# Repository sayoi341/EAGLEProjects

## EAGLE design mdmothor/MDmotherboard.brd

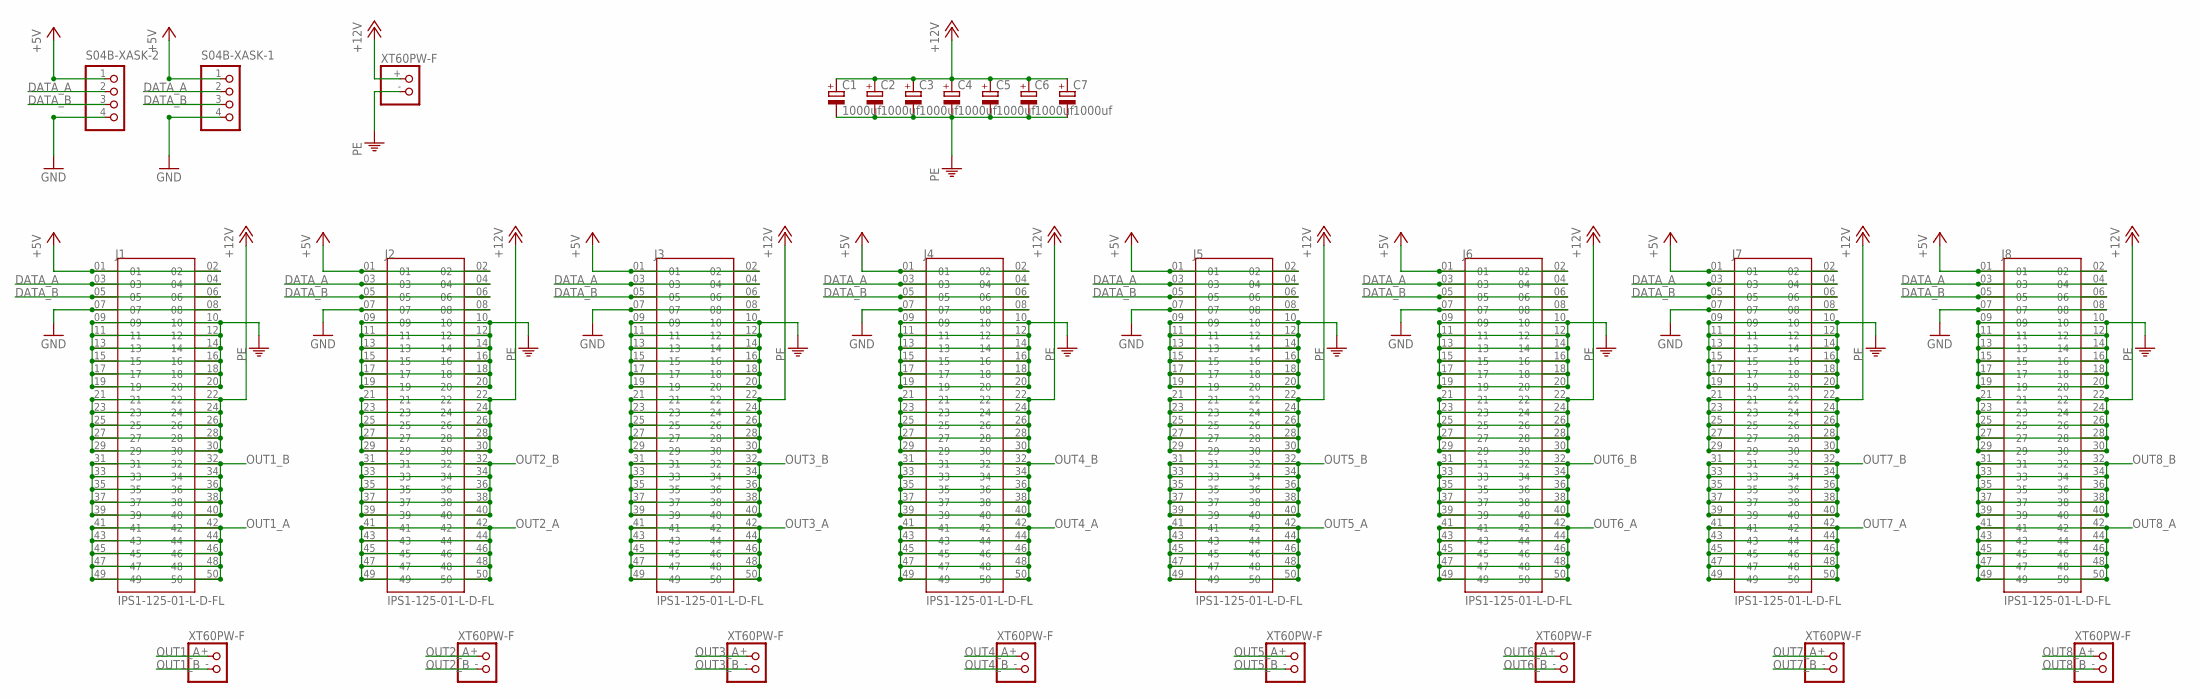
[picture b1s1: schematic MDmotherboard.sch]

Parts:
C1, C2, C3, C4, C5, C6, C7: 1000uf; E3,5-10
J1, J2, J3, J4, J5, J6, J7, J8: IPS1-125-01-L-D-FL; SAMTEC_IPS1-125-01-L-D-FL
S04B-XASK-1, S04B-XASK-2: S4B-XASK-1
U$1, U$2, U$3, U$4, U$5, U$6, U$7, U$8, U$9: XT60PW-F

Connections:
+5V: J1.01, J1.02, J2.01, J2.02, J3.01, J3.02, J4.01, J4.02, J5.01, J5.02, J6.01, J6.02, J7.01, J7.02, J8.01, J8.02, S04B-XASK-1.1, S04B-XASK-2.1
+12V: C1.+, C2.+, C3.+, C4.+, C5.+, C6.+, C7.+, J1.21, J1.22, J1.23, J1.24, J1.25, J1.26, J1.27, J1.28, J1.29, J1.30, J2.21, J2.22, J2.23, J2.24, J2.25, J2.26, J2.27, J2.28, J2.29, J2.30, J3.21, J3.22, J3.23, J3.24, J3.25, J3.26, J3.27, J3.28, J3.29, J3.30, J4.21, J4.22, J4.23, J4.24, J4.25, J4.26, J4.27, J4.28, J4.29, J4.30, J5.21, J5.22, J5.23, J5.24, J5.25, J5.26, J5.27, J5.28, J5.29, J5.30, J6.21, J6.22, J6.23, J6.24, J6.25, J6.26, J6.27, J6.28, J6.29, J6.30, J7.21, J7.22, J7.23, J7.24, J7.25, J7.26, J7.27, J7.28, J7.29, J7.30, J8.21, J8.22, J8.23, J8.24, J8.25, J8.26, J8.27, J8.28, J8.29, J8.30, U$1.+
DATA_A: J1.03, J1.04, J2.03, J2.04, J3.03, J3.04, J4.03, J4.04, J5.03, J5.04, J6.03, J6.04, J7.03, J7.04, J8.03, J8.04, S04B-XASK-1.2, S04B-XASK-2.2
DATA_B: J1.05, J1.06, J2.05, J2.06, J3.05, J3.06, J4.05, J4.06, J5.05, J5.06, J6.05, J6.06, J7.05, J7.06, J8.05, J8.06, S04B-XASK-1.3, S04B-XASK-2.3
GND: J1.07, J1.08, J2.07, J2.08, J3.07, J3.08, J4.07, J4.08, J5.07, J5.08, J6.07, J6.08, J7.07, J7.08, J8.07, J8.08, S04B-XASK-1.4, S04B-XASK-2.4
OUT1_A: J1.41, J1.42, J1.43, J1.44, J1.45, J1.46, J1.47, J1.48, J1.49, J1.50, U$2.+
OUT1_B: J1.31, J1.32, J1.33, J1.34, J1.35, J1.36, J1.37, J1.38, J1.39, J1.40, U$2.-
OUT2_A: J2.41, J2.42, J2.43, J2.44, J2.45, J2.46, J2.47, J2.48, J2.49, J2.50, U$3.+
OUT2_B: J2.31, J2.32, J2.33, J2.34, J2.35, J2.36, J2.37, J2.38, J2.39, J2.40, U$3.-
OUT3_A: J3.41, J3.42, J3.43, J3.44, J3.45, J3.46, J3.47, J3.48, J3.49, J3.50, U$4.+
OUT3_B: J3.31, J3.32, J3.33, J3.34, J3.35, J3.36, J3.37, J3.38, J3.39, J3.40, U$4.-
OUT4_A: J4.41, J4.42, J4.43, J4.44, J4.45, J4.46, J4.47, J4.48, J4.49, J4.50, U$5.+
OUT4_B: J4.31, J4.32, J4.33, J4.34, J4.35, J4.36, J4.37, J4.38, J4.39, J4.40, U$5.-
OUT5_A: J5.41, J5.42, J5.43, J5.44, J5.45, J5.46, J5.47, J5.48, J5.49, J5.50, U$6.+
OUT5_B: J5.31, J5.32, J5.33, J5.34, J5.35, J5.36, J5.37, J5.38, J5.39, J5.40, U$6.-
OUT6_A: J6.41, J6.42, J6.43, J6.44, J6.45, J6.46, J6.47, J6.48, J6.49, J6.50, U$7.+
OUT6_B: J6.31, J6.32, J6.33, J6.34, J6.35, J6.36, J6.37, J6.38, J6.39, J6.40, U$7.-
OUT7_A: J7.41, J7.42, J7.43, J7.44, J7.45, J7.46, J7.47, J7.48, J7.49, J7.50, U$8.+
OUT7_B: J7.31, J7.32, J7.33, J7.34, J7.35, J7.36, J7.37, J7.38, J7.39, J7.40, U$8.-
OUT8_A: J8.41, J8.42, J8.43, J8.44, J8.45, J8.46, J8.47, J8.48, J8.49, J8.50, U$9.+
OUT8_B: J8.31, J8.32, J8.33, J8.34, J8.35, J8.36, J8.37, J8.38, J8.39, J8.40, U$9.-
PE: C1.-, C2.-, C3.-, C4.-, C5.-, C6.-, C7.-, J1.09, J1.10, J1.11, J1.12, J1.13, J1.14, J1.15, J1.16, J1.17, J1.18, J1.19, J1.20, J2.09, J2.10, J2.11, J2.12, J2.13, J2.14, J2.15, J2.16, J2.17, J2.18, J2.19, J2.20, J3.09, J3.10, J3.11, J3.12, J3.13, J3.14, J3.15, J3.16, J3.17, J3.18, J3.19, J3.20, J4.09, J4.10, J4.11, J4.12, J4.13, J4.14, J4.15, J4.16, J4.17, J4.18, J4.19, J4.20, J5.09, J5.10, J5.11, J5.12, J5.13, J5.14, J5.15, J5.16, J5.17, J5.18, J5.19, J5.20, J6.09, J6.10, J6.11, J6.12, J6.13, J6.14, J6.15, J6.16, J6.17, J6.18, J6.19, J6.20, J7.09, J7.10, J7.11, J7.12, J7.13, J7.14, J7.15, J7.16, J7.17, J7.18, J7.19, J7.20, J8.09, J8.10, J8.11, J8.12, J8.13, J8.14, J8.15, J8.16, J8.17, J8.18, J8.19, J8.20, U$1.-

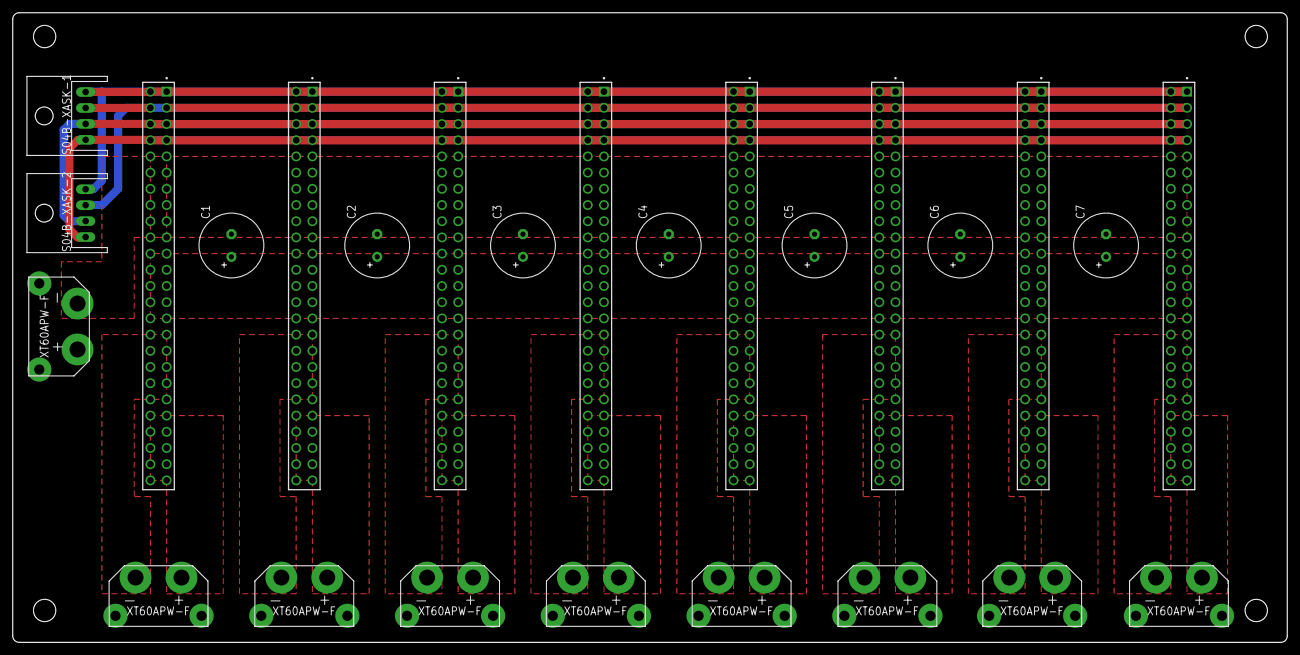
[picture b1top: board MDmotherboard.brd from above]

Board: 2 copper layers, 199.9 x 98.7 mm, 26 parts (0 on the bottom side), 22 nets.

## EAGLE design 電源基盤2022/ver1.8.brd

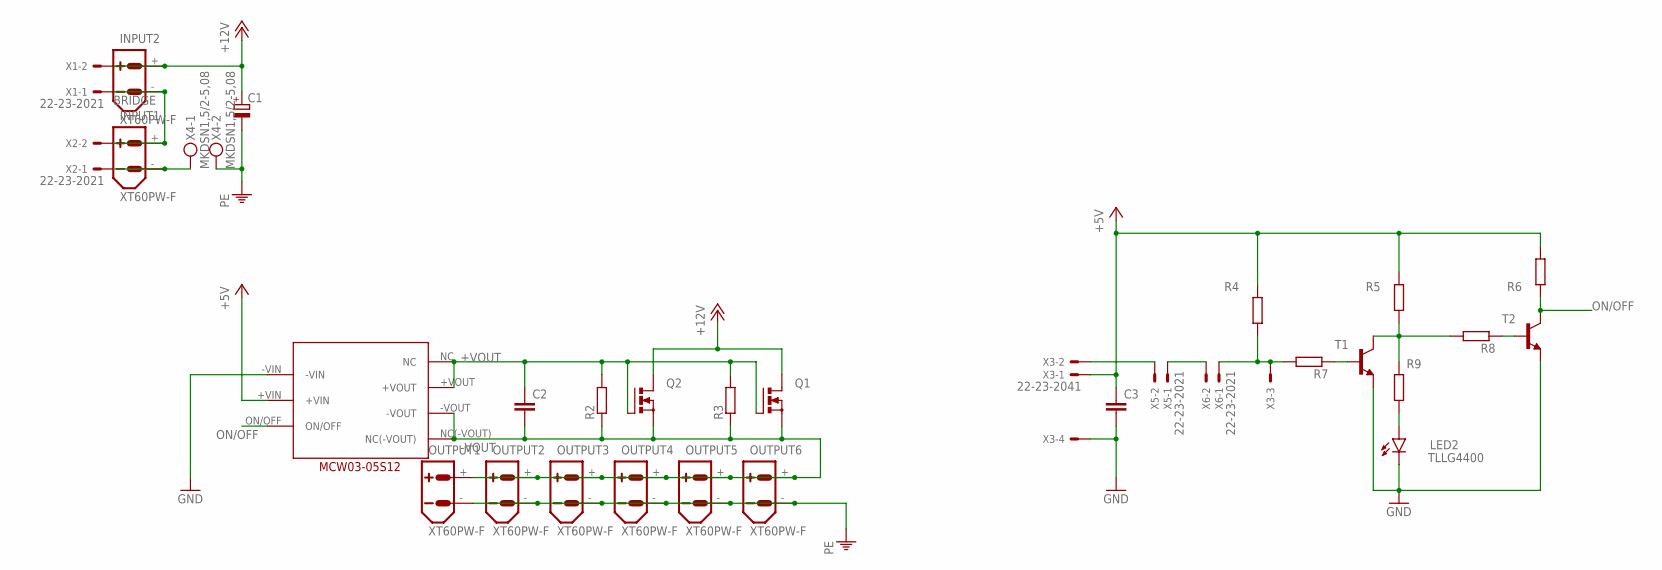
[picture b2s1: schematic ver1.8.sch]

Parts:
C1: CPOL-EUE3.5-10; E3,5-10
C2, C3: C-EU025-030X050; C025-030X050
INPUT1, INPUT2: XT60PW-F
LED2: TLLG4400; LED3MM
OUTPUT1, OUTPUT2, OUTPUT3, OUTPUT4, OUTPUT5, OUTPUT6: XT60PW-F
Q1, Q2: PMOSFET_NTO220BV; TO220BV
R2, R3, R4, R5, R6, R7, R8, R9: R-EU_0204/5; 0204/5
T1, T2: -NPN-TO92-ECB; TO92-ECB
U$3: MCW03-05S12
X1, X2, X5, X6: 22-23-2021
X3: 22-23-2041
X4: MKDSN1,5/2-5,08

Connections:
+5V: C3.1, R4.2, R5.2, R6.2, U$3.+VIN, X3.1
+12V: C1.+, INPUT2.+, Q1.D, Q2.D, X1.2
+VOUT: C2.1, Q1.G, Q2.G, R2.2, R3.2, U$3.+VOUT, U$3.NC
-VOUT: C2.2, OUTPUT1.+, OUTPUT2.+, OUTPUT3.+, OUTPUT4.+, OUTPUT5.+, OUTPUT6.+, Q1.S, Q2.S, R2.1, R3.1, U$3.-VOUT, U$3.NC(-VOUT)
BRIDGE: INPUT1.+, INPUT2.-, X1.1, X2.2
GND: C3.2, LED2.K (C), T1.E, T2.E, U$3.-VIN, X3.4
unnamed: INPUT1.-, X2.1, X4.1
unnamed: X3.2, X5.2
unnamed: X5.1, X6.2
unnamed: R4.1, R7.2, X3.3, X6.1
unnamed: R7.1, T1.B
unnamed: R5.1, R8.2, R9.1, T1.C
unnamed: R8.1, T2.B
unnamed: LED2.A, R9.2
ON/OFF: R6.1, T2.C, U$3.ON/OFF
PE: C1.-, OUTPUT1.-, OUTPUT2.-, OUTPUT3.-, OUTPUT4.-, OUTPUT5.-, OUTPUT6.-, X4.2

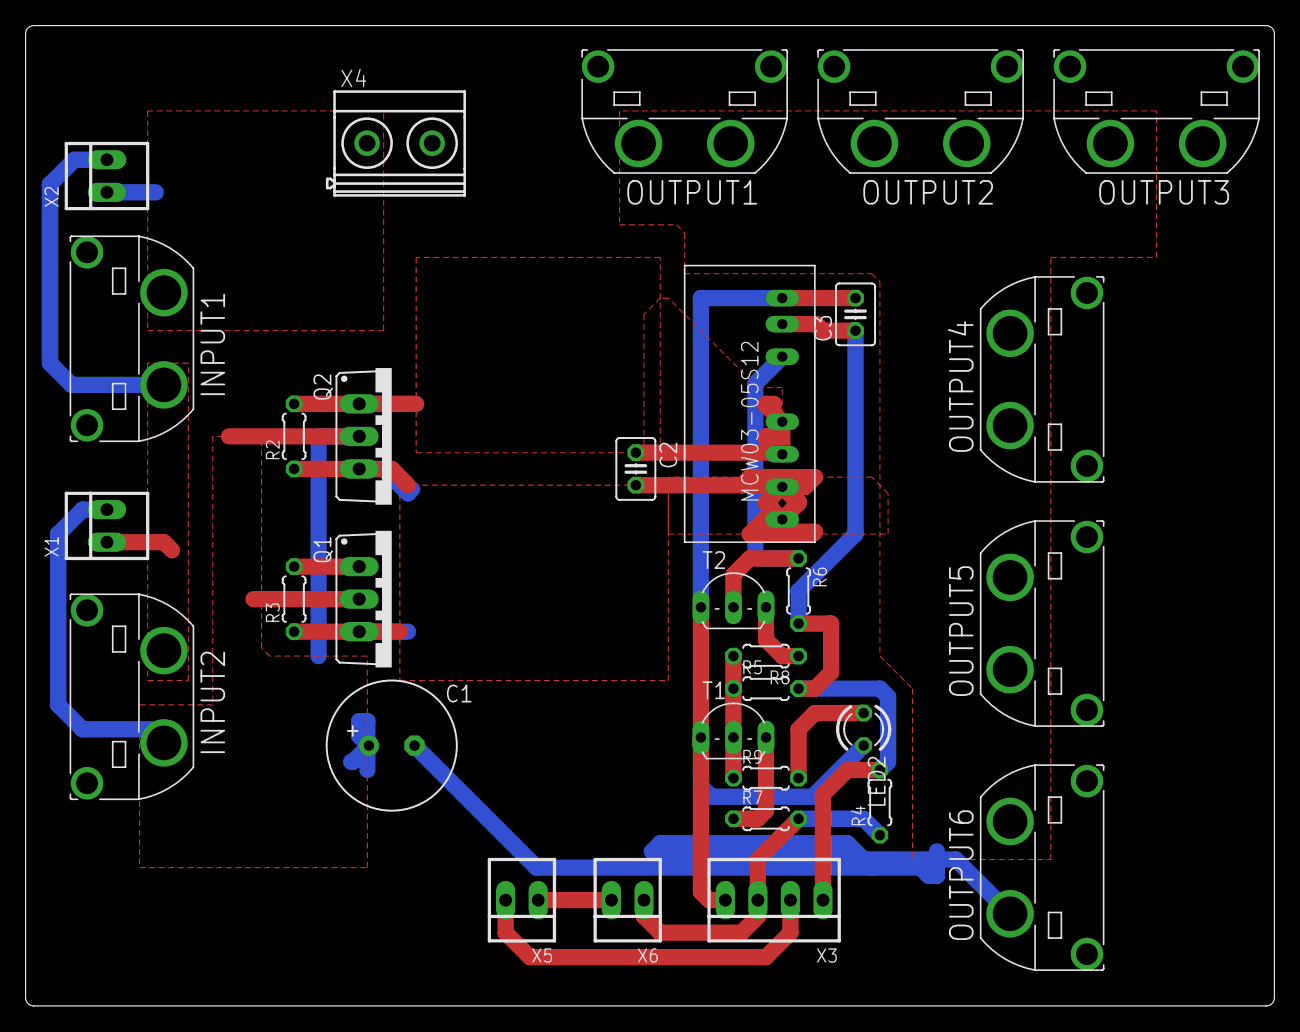
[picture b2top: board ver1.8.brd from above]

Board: 2 copper layers, 97.5 x 76.5 mm, 31 parts (0 on the bottom side), 16 nets.
